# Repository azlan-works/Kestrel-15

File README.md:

# Kestrel-15: An Opensource FPGA SoM based on the Gowin GW5AT-15

1mm JLCPCB 6-layer 7628 stackup:

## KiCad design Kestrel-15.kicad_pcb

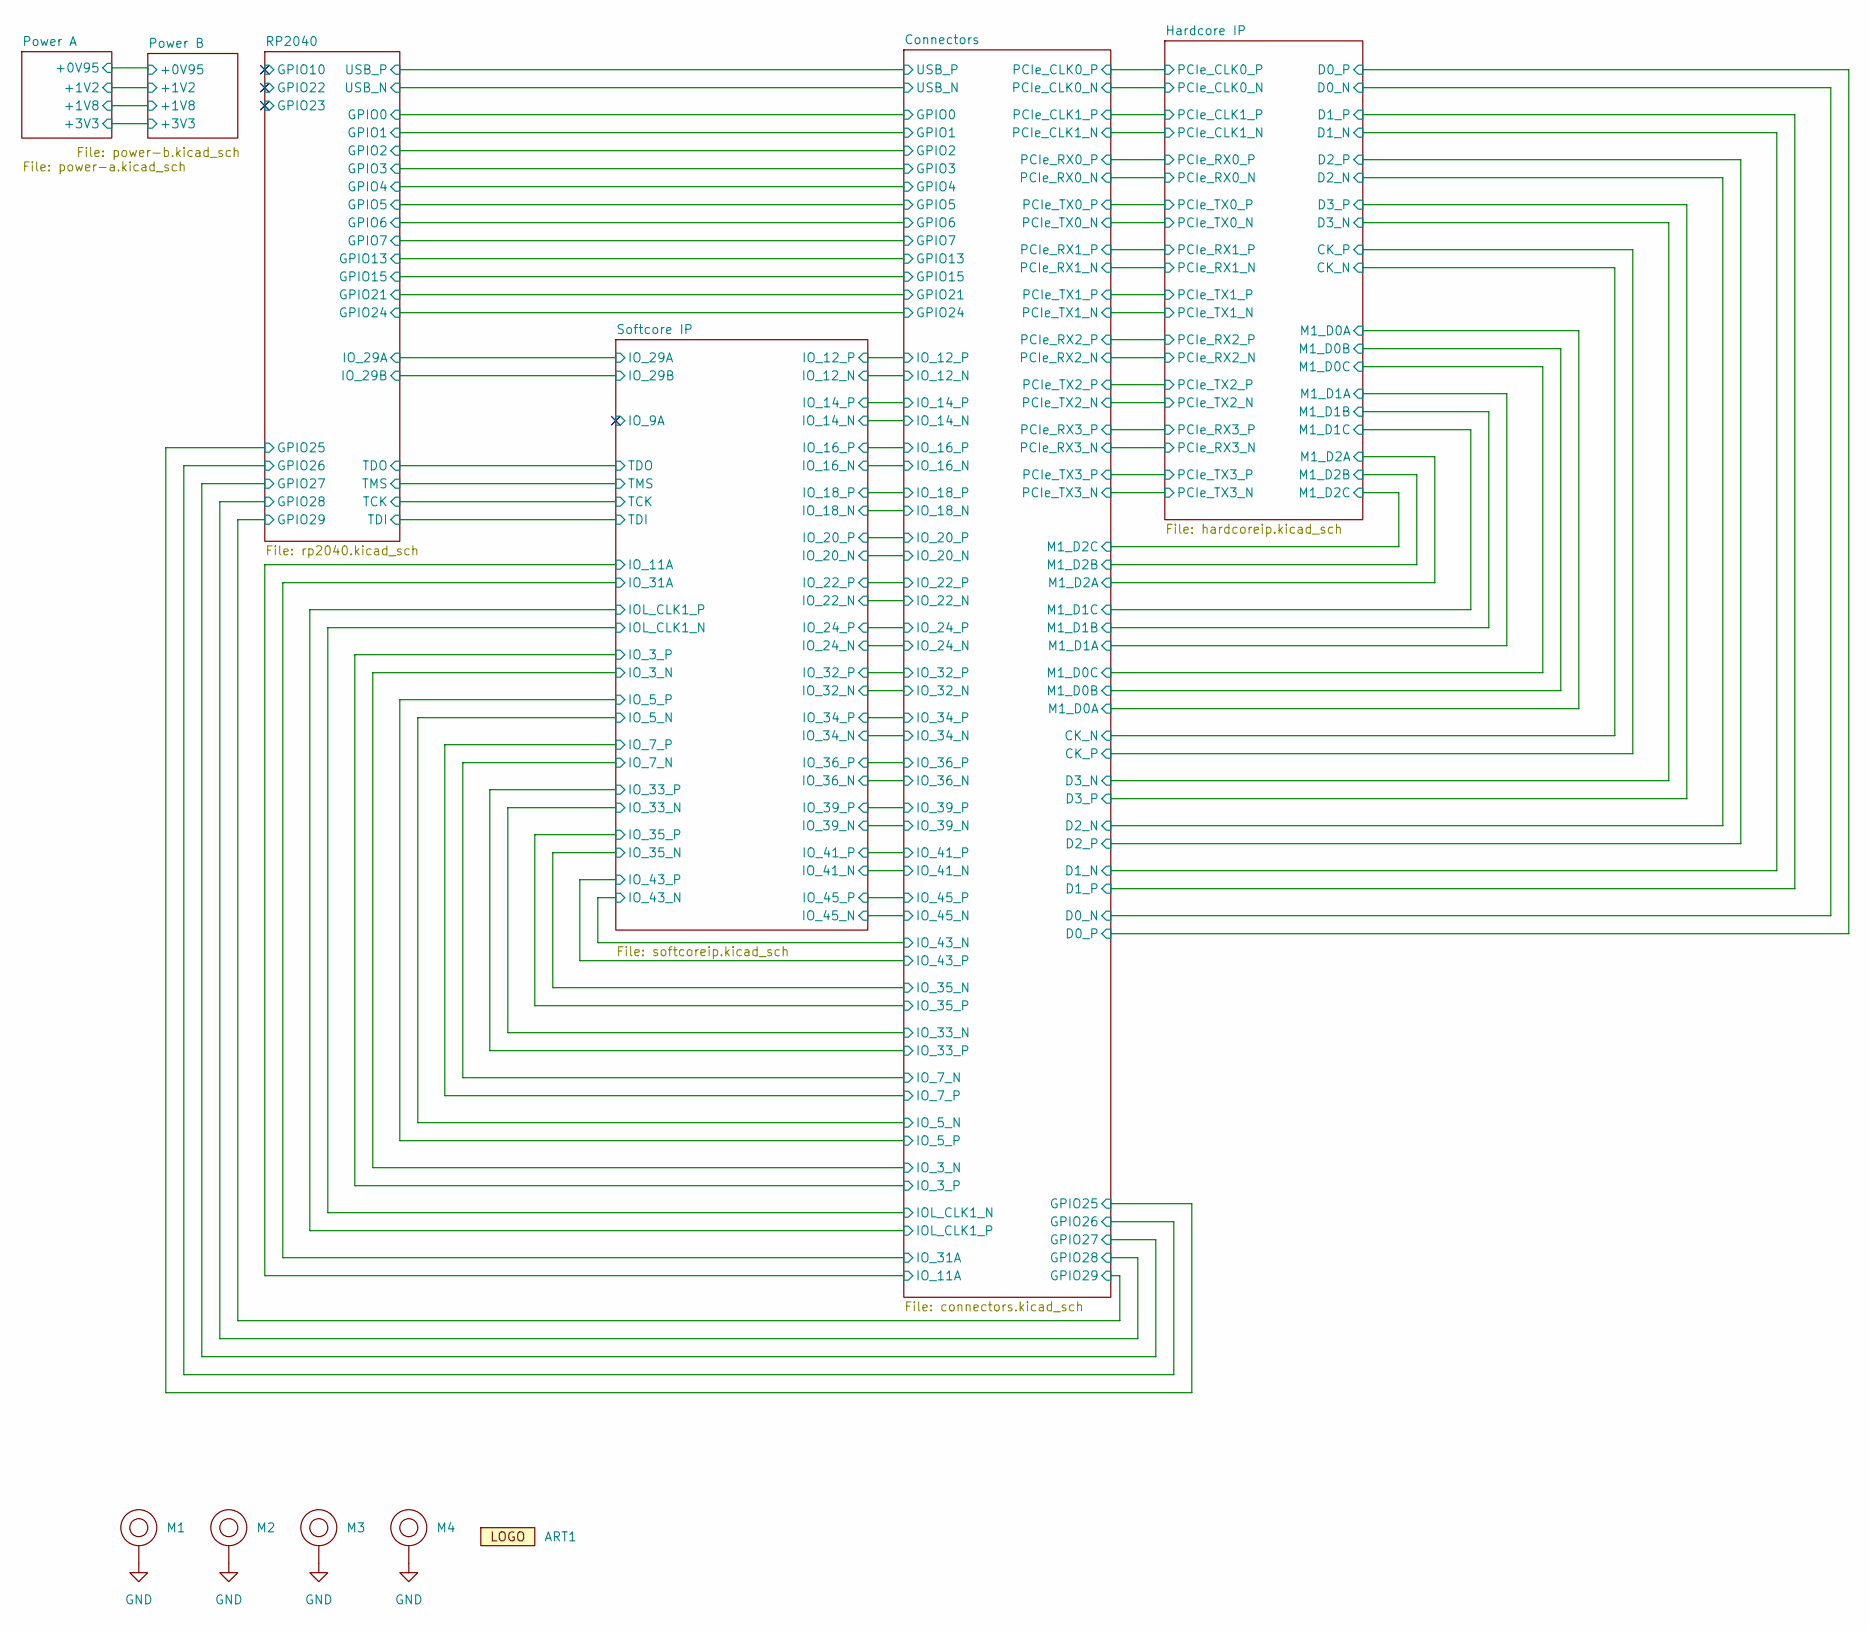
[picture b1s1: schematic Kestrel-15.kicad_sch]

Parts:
ART1: azlan.works_logo
M1, M2, M3, M4: M2_Hole

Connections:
GND: M1.1 (1_1), M2.1 (1_1), M3.1 (1_1), M4.1 (1_1); also elsewhere on the board

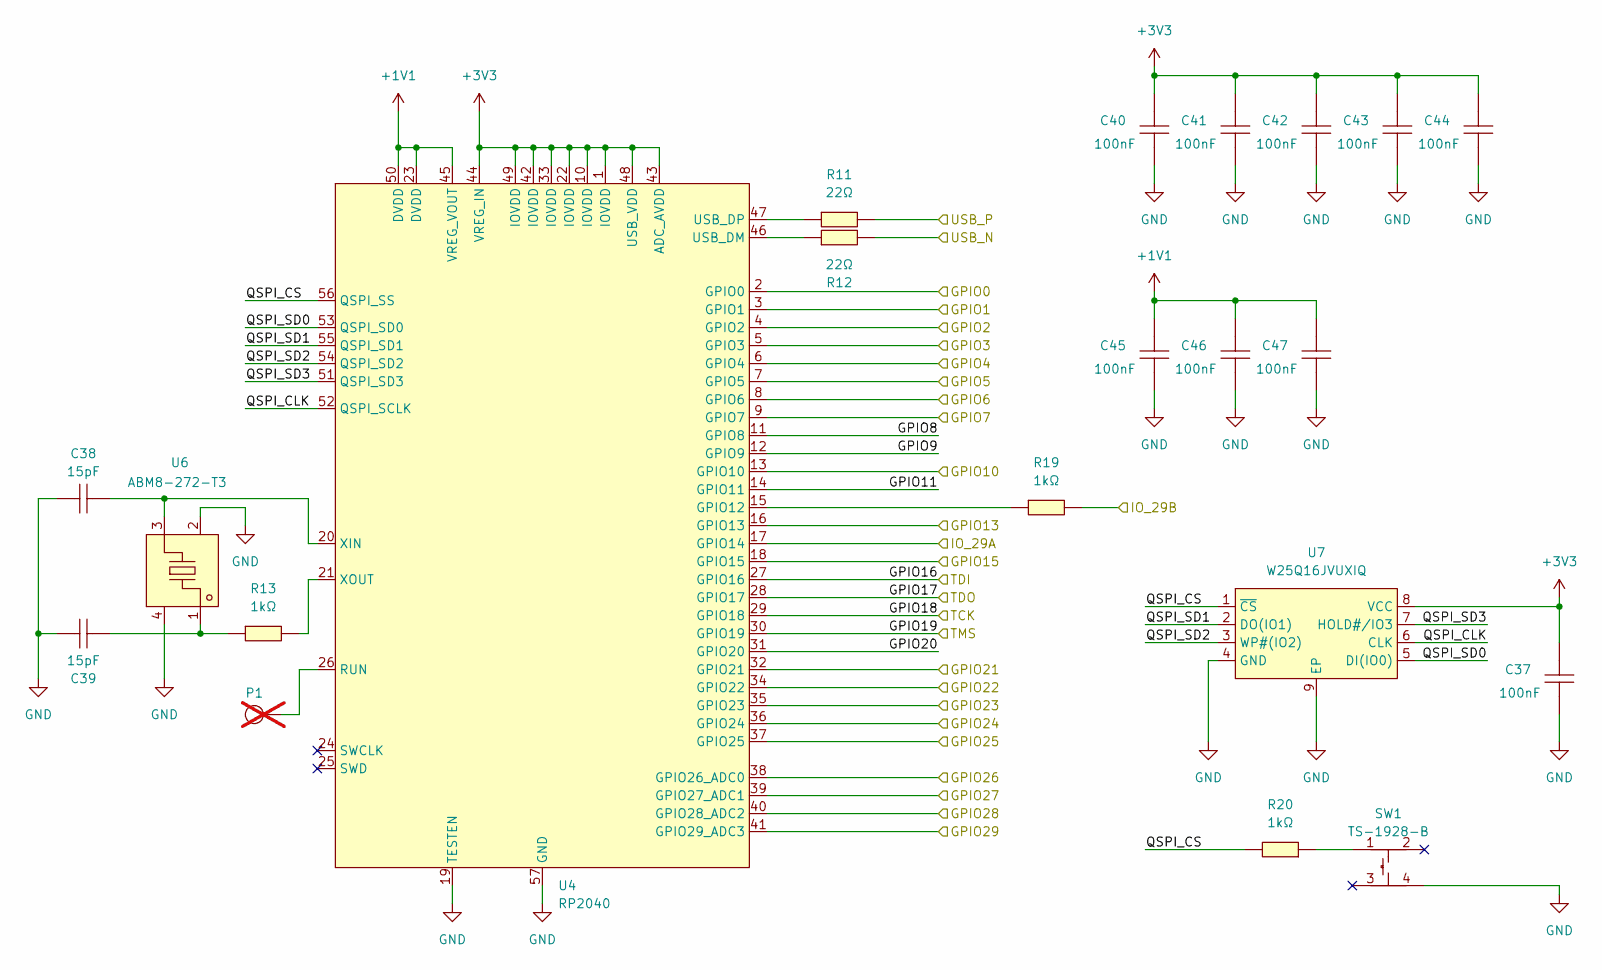
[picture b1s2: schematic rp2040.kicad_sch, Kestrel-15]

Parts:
C37, C40, C41, C42, C43, C44, C45, C46, C47: 100nF; C0201; MPN 0201X104M250NT; LCSC Part C52033358
C38, C39: 15pF; C0402; MPN 0402CG150J500NT; LCSC Part C1548
P1: Pogo Pin; TESTPOINT-SMD_BD2.0_C9900030651; MPN YTC1P-3010-01; LCSC Part C5221282; not fitted
R11, R12: 22Ω; R0402; MPN 0402WGF220JTCE; LCSC Part C25092
R13, R19, R20: 1kΩ; R0201; MPN 0201WMF1001TEE; LCSC Part C270365
SW1: TS-1928-B; KEY-SMD_4P-L2.8-W2.0-P1.20-LS3.0-TL; LCSC Part C1121891
U4: RP2040; LQFN-56_L7.0-W7.0-P0.4-EP; MPN RP2040; LCSC Part C2040
U6: ABM8-272-T3; CRYSTAL-SMD_4P-L3.2-W2.5-BL; MPN ABM8-272-T3; LCSC Part C20625731
U7: W25Q16JVUXIQ; USON-8_L3.0-W2.0-P0.50-BL-EP; MPN W25Q16JVUXIQ; LCSC Part C2843335

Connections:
+1V1: C45.2, C46.2, C47.2, U4.23 (DVDD), U4.45 (VREG_VOUT), U4.50 (DVDD)
+3V3: C37.2, C40.2, C41.2, C42.2, C43.2, C44.2, U4.1 (IOVDD), U4.10 (IOVDD), U4.22 (IOVDD), U4.33 (IOVDD), U4.42 (IOVDD), U4.43 (ADC_AVDD), U4.44 (VREG_IN), U4.48 (USB_VDD), U4.49 (IOVDD), U7.8 (VCC); also elsewhere on the board
/Connectors/GPIO0: U4.2 (GPIO0); also elsewhere on the board
/Connectors/GPIO1: U4.3 (GPIO1); also elsewhere on the board
/Connectors/GPIO2: U4.4 (GPIO2); also elsewhere on the board
/Connectors/GPIO3: U4.5 (GPIO3); also elsewhere on the board
/Connectors/GPIO4: U4.6 (GPIO4); also elsewhere on the board
/Connectors/GPIO5: U4.7 (GPIO5); also elsewhere on the board
/Connectors/GPIO6: U4.8 (GPIO6); also elsewhere on the board
/Connectors/GPIO7: U4.9 (GPIO7); also elsewhere on the board
/Connectors/GPIO13: U4.16 (GPIO13); also elsewhere on the board
/Connectors/GPIO15: U4.18 (GPIO15); also elsewhere on the board
/Connectors/GPIO21: U4.32 (GPIO21); also elsewhere on the board
/Connectors/GPIO24: U4.36 (GPIO24); also elsewhere on the board
/Connectors/GPIO25: U4.37 (GPIO25); also elsewhere on the board
/Connectors/GPIO26: U4.38 (GPIO26_ADC0); also elsewhere on the board
/Connectors/GPIO27: U4.39 (GPIO27_ADC1); also elsewhere on the board
/Connectors/GPIO28: U4.40 (GPIO28_ADC2); also elsewhere on the board
/Connectors/GPIO29: U4.41 (GPIO29_ADC3); also elsewhere on the board
/Connectors/USB_N: R12.2; also elsewhere on the board
/Connectors/USB_P: R11.2; also elsewhere on the board
/RP2040/GPIO8: U4.11 (GPIO8)
/RP2040/GPIO9: U4.12 (GPIO9)
/RP2040/GPIO10: U4.13 (GPIO10)
/RP2040/GPIO11: U4.14 (GPIO11)
/RP2040/GPIO16: U4.27 (GPIO16); also elsewhere on the board
/RP2040/GPIO17: U4.28 (GPIO17); also elsewhere on the board
/RP2040/GPIO18: U4.29 (GPIO18); also elsewhere on the board
/RP2040/GPIO19: U4.30 (GPIO19); also elsewhere on the board
/RP2040/GPIO20: U4.31 (GPIO20)
/RP2040/GPIO22: U4.34 (GPIO22)
/RP2040/GPIO23: U4.35 (GPIO23)
/RP2040/IO_29A: U4.17 (GPIO14); also elsewhere on the board
/RP2040/IO_29B: R19.2; also elsewhere on the board
/RP2040/QSPI_CLK: U4.52 (QSPI_SCLK), U7.6 (CLK)
/RP2040/QSPI_CS: R20.2, U4.56 (QSPI_SS), U7.1 (~CS)
/RP2040/QSPI_SD0: U4.53 (QSPI_SD0), U7.5 (DI(IO0))
/RP2040/QSPI_SD1: U4.55 (QSPI_SD1), U7.2 (DO(IO1))
/RP2040/QSPI_SD2: U4.54 (QSPI_SD2), U7.3 (WP#(IO2))
/RP2040/QSPI_SD3: U4.51 (QSPI_SD3), U7.7 (HOLD#/IO3)
GND: C37.1, C38.1, C39.1, C40.1, C41.1, C42.1, C43.1, C44.1, C45.1, C46.1, C47.1, SW1.4, U4.19 (TESTEN), U4.57 (GND), U6.2 (GND), U6.4 (GND), U7.4 (GND), U7.9 (EP); also elsewhere on the board
unnamed: C39.2, R13.1, U6.1
unnamed: R20.1, SW1.1
unnamed: R19.1, U4.15 (GPIO12)
unnamed: P1.1 (1_1), U4.26 (RUN)
unnamed: R12.1, U4.46 (USB_DM)
unnamed: R11.1, U4.47 (USB_DP)
unnamed: C38.2, U4.20 (XIN), U6.3
unnamed: R13.2, U4.21 (XOUT)

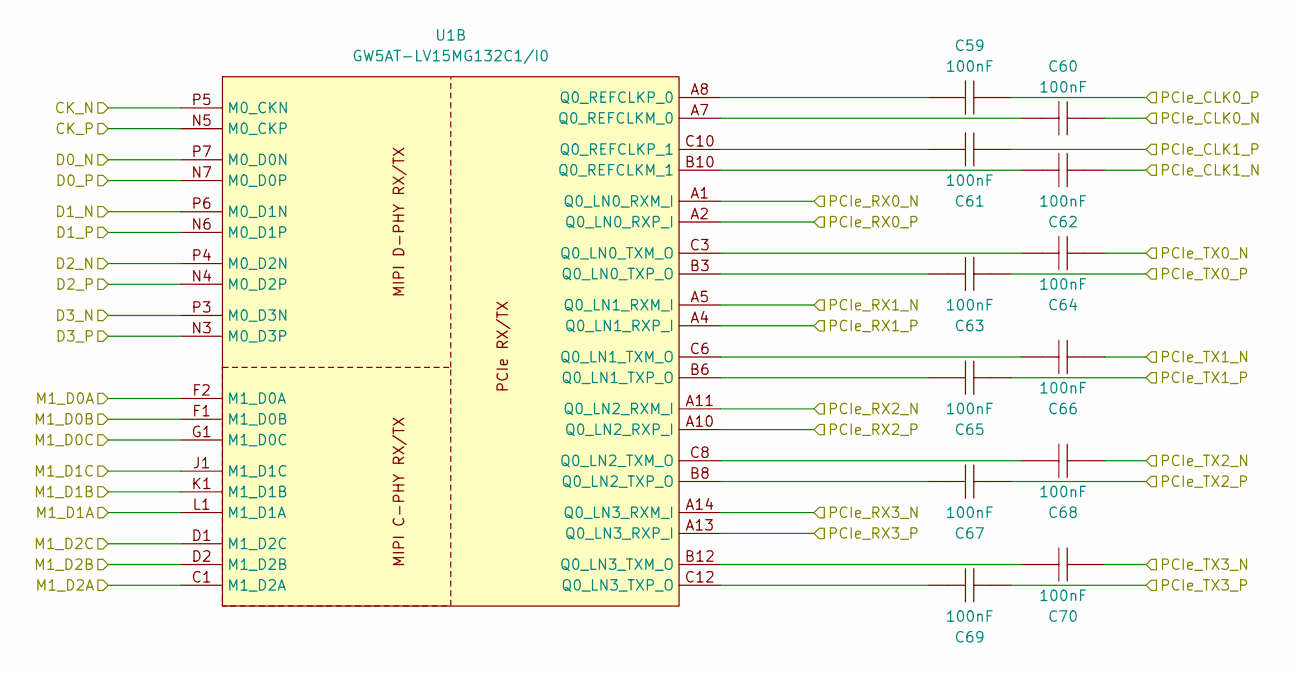
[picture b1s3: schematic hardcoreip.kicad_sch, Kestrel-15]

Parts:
C59, C60, C61, C62, C63, C64, C65, C66, C67, C68, C69, C70: 100nF; C0201; MPN 0201X104M250NT; LCSC Part C52033358
U1: GW5AT-LV15MG132C1/I0; CSBGA-132_L8.0-W8.0-P0.50-TL_GW1N-2K-MG132X1; MPN GW5AT-LV15MG132C1/I0; LCSC Part C54067362

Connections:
/Connectors/CK_N: U1.P5 (M0_CKN); also elsewhere on the board
/Connectors/CK_P: U1.N5 (M0_CKP); also elsewhere on the board
/Connectors/D0_N: U1.P7 (M0_D0N); also elsewhere on the board
/Connectors/D0_P: U1.N7 (M0_D0P); also elsewhere on the board
/Connectors/D1_N: U1.P6 (M0_D1N); also elsewhere on the board
/Connectors/D1_P: U1.N6 (M0_D1P); also elsewhere on the board
/Connectors/D2_N: U1.P4 (M0_D2N); also elsewhere on the board
/Connectors/D2_P: U1.N4 (M0_D2P); also elsewhere on the board
/Connectors/D3_N: U1.P3 (M0_D3N); also elsewhere on the board
/Connectors/D3_P: U1.N3 (M0_D3P); also elsewhere on the board
/Connectors/M1_D0A: U1.F2 (M1_D0A); also elsewhere on the board
/Connectors/M1_D0B: U1.F1 (M1_D0B); also elsewhere on the board
/Connectors/M1_D0C: U1.G1 (M1_D0C); also elsewhere on the board
/Connectors/M1_D1A: U1.L1 (M1_D1A); also elsewhere on the board
/Connectors/M1_D1B: U1.K1 (M1_D1B); also elsewhere on the board
/Connectors/M1_D1C: U1.J1 (M1_D1C); also elsewhere on the board
/Connectors/M1_D2A: U1.C1 (M1_D2A); also elsewhere on the board
/Connectors/M1_D2B: U1.D2 (M1_D2B); also elsewhere on the board
/Connectors/M1_D2C: U1.D1 (M1_D2C); also elsewhere on the board
/Connectors/PCIe_CLK0_N: C60.2; also elsewhere on the board
/Connectors/PCIe_CLK0_P: C59.2; also elsewhere on the board
/Connectors/PCIe_CLK1_N: C62.2; also elsewhere on the board
/Connectors/PCIe_CLK1_P: C61.2; also elsewhere on the board
/Connectors/PCIe_RX0_N: U1.A1 (Q0_LN0_RXM_I); also elsewhere on the board
/Connectors/PCIe_RX0_P: U1.A2 (Q0_LN0_RXP_I); also elsewhere on the board
/Connectors/PCIe_RX1_N: U1.A5 (Q0_LN1_RXM_I); also elsewhere on the board
/Connectors/PCIe_RX1_P: U1.A4 (Q0_LN1_RXP_I); also elsewhere on the board
/Connectors/PCIe_RX2_N: U1.A11 (Q0_LN2_RXM_I); also elsewhere on the board
/Connectors/PCIe_RX2_P: U1.A10 (Q0_LN2_RXP_I); also elsewhere on the board
/Connectors/PCIe_RX3_N: U1.A14 (Q0_LN3_RXM_I); also elsewhere on the board
/Connectors/PCIe_RX3_P: U1.A13 (Q0_LN3_RXP_I); also elsewhere on the board
/Connectors/PCIe_TX0_N: C64.2; also elsewhere on the board
/Connectors/PCIe_TX0_P: C63.2; also elsewhere on the board
/Connectors/PCIe_TX1_N: C66.2; also elsewhere on the board
/Connectors/PCIe_TX1_P: C65.2; also elsewhere on the board
/Connectors/PCIe_TX2_N: C68.2; also elsewhere on the board
/Connectors/PCIe_TX2_P: C67.2; also elsewhere on the board
/Connectors/PCIe_TX3_N: C70.2; also elsewhere on the board
/Connectors/PCIe_TX3_P: C69.2; also elsewhere on the board
unnamed: C64.1, U1.C3 (Q0_LN0_TXM_O)
unnamed: C63.1, U1.B3 (Q0_LN0_TXP_O)
unnamed: C66.1, U1.C6 (Q0_LN1_TXM_O)
unnamed: C65.1, U1.B6 (Q0_LN1_TXP_O)
unnamed: C68.1, U1.C8 (Q0_LN2_TXM_O)
unnamed: C67.1, U1.B8 (Q0_LN2_TXP_O)
unnamed: C70.1, U1.B12 (Q0_LN3_TXM_O)
unnamed: C69.1, U1.C12 (Q0_LN3_TXP_O)
unnamed: C60.1, U1.A7 (Q0_REFCLKM_0)
unnamed: C62.1, U1.B10 (Q0_REFCLKM_1)
unnamed: C59.1, U1.A8 (Q0_REFCLKP_0)
unnamed: C61.1, U1.C10 (Q0_REFCLKP_1)

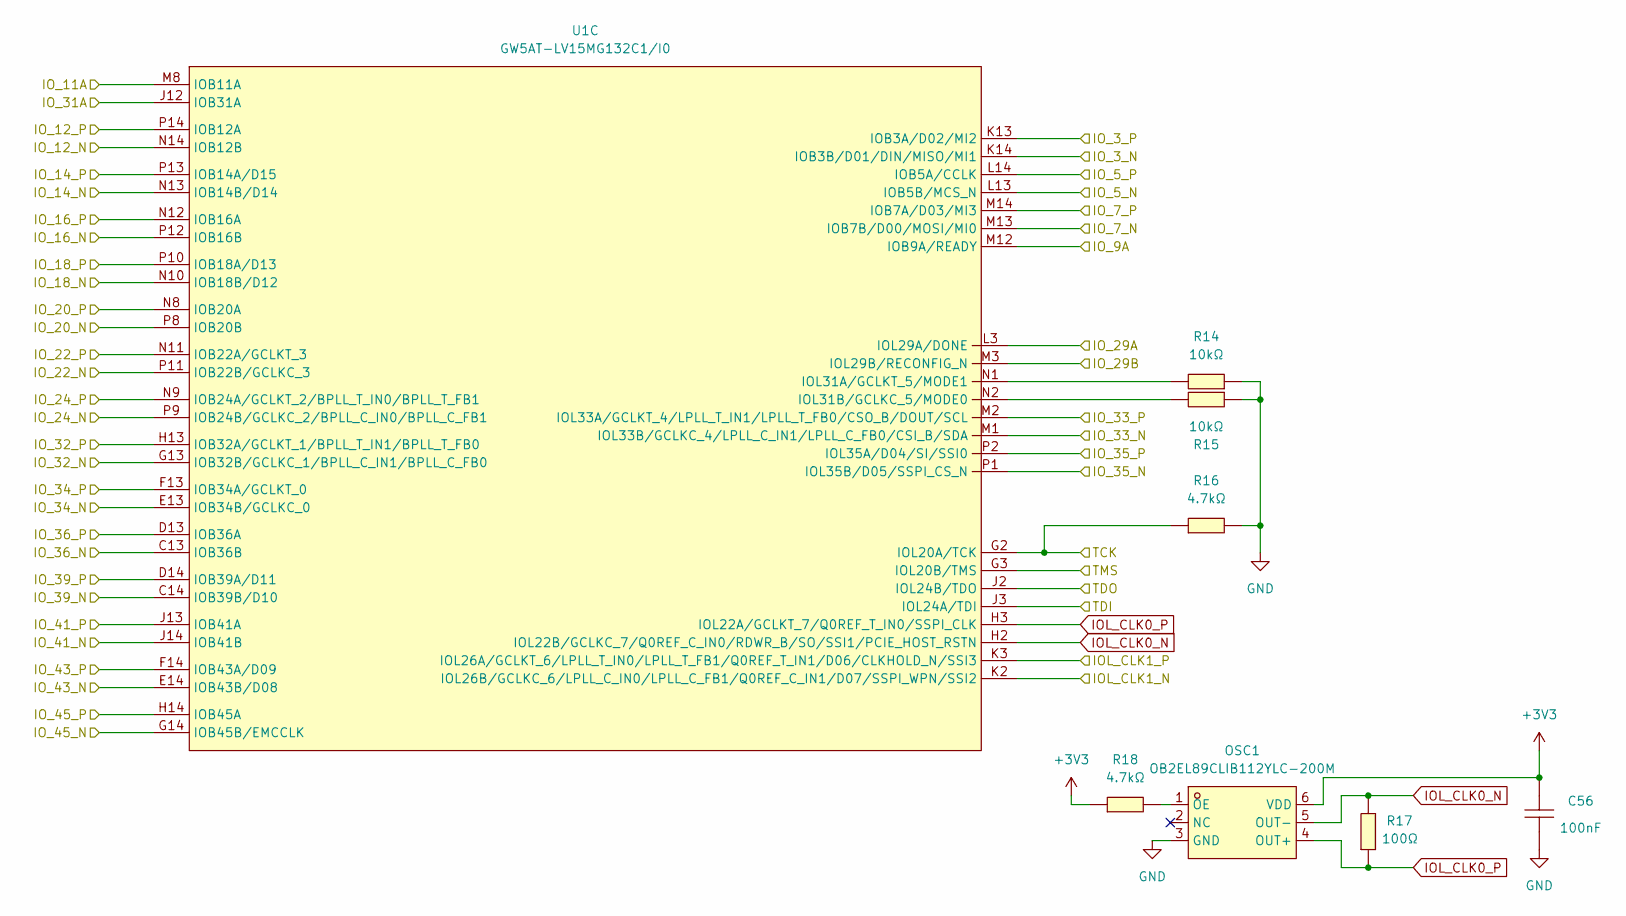
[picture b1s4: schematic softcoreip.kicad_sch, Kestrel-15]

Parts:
C56: 100nF; C0201; MPN 0201X104M250NT; LCSC Part C52033358
OSC1: OB2EL89CLIB112YLC-200M; OSC-SMD_6P-L3.2-W2.5-BL-1; MPN OB2EL89CLIB112YLC-200M; LCSC Part C41371042
R14, R15: 10kΩ; R0402; MPN 0402WGF1002TCE; LCSC Part C25744
R16, R18: 4.7kΩ; R0402; MPN 0402WGF4701TCE; LCSC Part C25900
R17: 100Ω; R0402; MPN 0402WGF1000TCE; LCSC Part C25076
U1: GW5AT-LV15MG132C1/I0; CSBGA-132_L8.0-W8.0-P0.50-TL_GW1N-2K-MG132X1; MPN GW5AT-LV15MG132C1/I0; LCSC Part C54067362

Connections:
+3V3: C56.2, OSC1.6 (VDD), R18.1; also elsewhere on the board
/Connectors/IOL_CLK1_N: U1.K2 (IOL26B/GCLKC_6/LPLL_C_IN0/LPLL_C_FB1/Q0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); also elsewhere on the board
/Connectors/IOL_CLK1_P: U1.K3 (IOL26A/GCLKT_6/LPLL_T_IN0/LPLL_T_FB1/Q0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); also elsewhere on the board
/Connectors/IO_3_N: U1.K14 (IOB3B/D01/DIN/MISO/MI1); also elsewhere on the board
/Connectors/IO_3_P: U1.K13 (IOB3A/D02/MI2); also elsewhere on the board
/Connectors/IO_5_N: U1.L13 (IOB5B/MCS_N); also elsewhere on the board
/Connectors/IO_5_P: U1.L14 (IOB5A/CCLK); also elsewhere on the board
/Connectors/IO_7_N: U1.M13 (IOB7B/D00/MOSI/MI0); also elsewhere on the board
/Connectors/IO_7_P: U1.M14 (IOB7A/D03/MI3); also elsewhere on the board
/Connectors/IO_11A: U1.M8 (IOB11A); also elsewhere on the board
/Connectors/IO_12_N: U1.N14 (IOB12B); also elsewhere on the board
/Connectors/IO_12_P: U1.P14 (IOB12A); also elsewhere on the board
/Connectors/IO_14_N: U1.N13 (IOB14B/D14); also elsewhere on the board
/Connectors/IO_14_P: U1.P13 (IOB14A/D15); also elsewhere on the board
/Connectors/IO_16_N: U1.P12 (IOB16B); also elsewhere on the board
/Connectors/IO_16_P: U1.N12 (IOB16A); also elsewhere on the board
/Connectors/IO_18_N: U1.N10 (IOB18B/D12); also elsewhere on the board
/Connectors/IO_18_P: U1.P10 (IOB18A/D13); also elsewhere on the board
/Connectors/IO_20_N: U1.P8 (IOB20B); also elsewhere on the board
/Connectors/IO_20_P: U1.N8 (IOB20A); also elsewhere on the board
/Connectors/IO_22_N: U1.P11 (IOB22B/GCLKC_3); also elsewhere on the board
/Connectors/IO_22_P: U1.N11 (IOB22A/GCLKT_3); also elsewhere on the board
/Connectors/IO_24_N: U1.P9 (IOB24B/GCLKC_2/BPLL_C_IN0/BPLL_C_FB1); also elsewhere on the board
/Connectors/IO_24_P: U1.N9 (IOB24A/GCLKT_2/BPLL_T_IN0/BPLL_T_FB1); also elsewhere on the board
/Connectors/IO_31A: U1.J12 (IOB31A); also elsewhere on the board
/Connectors/IO_32_N: U1.G13 (IOB32B/GCLKC_1/BPLL_C_IN1/BPLL_C_FB0); also elsewhere on the board
/Connectors/IO_32_P: U1.H13 (IOB32A/GCLKT_1/BPLL_T_IN1/BPLL_T_FB0); also elsewhere on the board
/Connectors/IO_33_N: U1.M1 (IOL33B/GCLKC_4/LPLL_C_IN1/LPLL_C_FB0/CS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); also elsewhere on the board
/Connectors/IO_33_P: U1.M2 (IOL33A/GCLKT_4/LPLL_T_IN1/LPLL_T_FB0/CS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); also elsewhere on the board
/Connectors/IO_34_N: U1.E13 (IOB34B/GCLKC_0); also elsewhere on the board
/Connectors/IO_34_P: U1.F13 (IOB34A/GCLKT_0); also elsewhere on the board
/Connectors/IO_35_N: U1.P1 (IOL35B/D05/SSPI_CS_N); also elsewhere on the board
/Connectors/IO_35_P: U1.P2 (IOL35A/D04/SI/SSI0); also elsewhere on the board
/Connectors/IO_36_N: U1.C13 (IOB36B); also elsewhere on the board
/Connectors/IO_36_P: U1.D13 (IOB36A); also elsewhere on the board
/Connectors/IO_39_N: U1.C14 (IOB39B/D10); also elsewhere on the board
/Connectors/IO_39_P: U1.D14 (IOB39A/D11); also elsewhere on the board
/Connectors/IO_41_N: U1.J14 (IOB41B); also elsewhere on the board
/Connectors/IO_41_P: U1.J13 (IOB41A); also elsewhere on the board
/Connectors/IO_43_N: U1.E14 (IOB43B/D08); also elsewhere on the board
/Connectors/IO_43_P: U1.F14 (IOB43A/D09); also elsewhere on the board
/Connectors/IO_45_N: U1.G14 (IOB45B/EMCCLK); also elsewhere on the board
/Connectors/IO_45_P: U1.H14 (IOB45A); also elsewhere on the board
/RP2040/GPIO16: U1.J3 (IOL24A/TDI); also elsewhere on the board
/RP2040/GPIO17: U1.J2 (IOL24B/TDO); also elsewhere on the board
/RP2040/GPIO18: R16.1, U1.G2 (IOL20A/TCK); also elsewhere on the board
/RP2040/GPIO19: U1.G3 (IOL20B/TMS); also elsewhere on the board
/RP2040/IO_29A: U1.L3 (IOL29A/DONE); also elsewhere on the board
/RP2040/IO_29B: U1.M3 (IOL29B/RECONFIG_N); also elsewhere on the board
/Softcore IP/IO_9A: U1.M12 (IOB9A/READY)
GND: C56.1, OSC1.3 (GND), R14.1, R15.1, R16.2; also elsewhere on the board
IOL_CLK0_N: OSC1.5 (OUT-), R17.2, U1.H2 (IOL22B/GCLKC_7/Q0REF_C_IN0/RDWR_B/SO/SS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)
IOL_CLK0_P: OSC1.4 (OUT+), R17.1, U1.H3 (IOL22A/GCLKT_7/Q0REF_T_IN0/SSPI_CLK)
unnamed: OSC1.1 (OE), R18.2
unnamed: R14.2, U1.N1 (IOL31A/GCLKT_5/MODE1)
unnamed: R15.2, U1.N2 (IOL31B/GCLKC_5/MODE0)

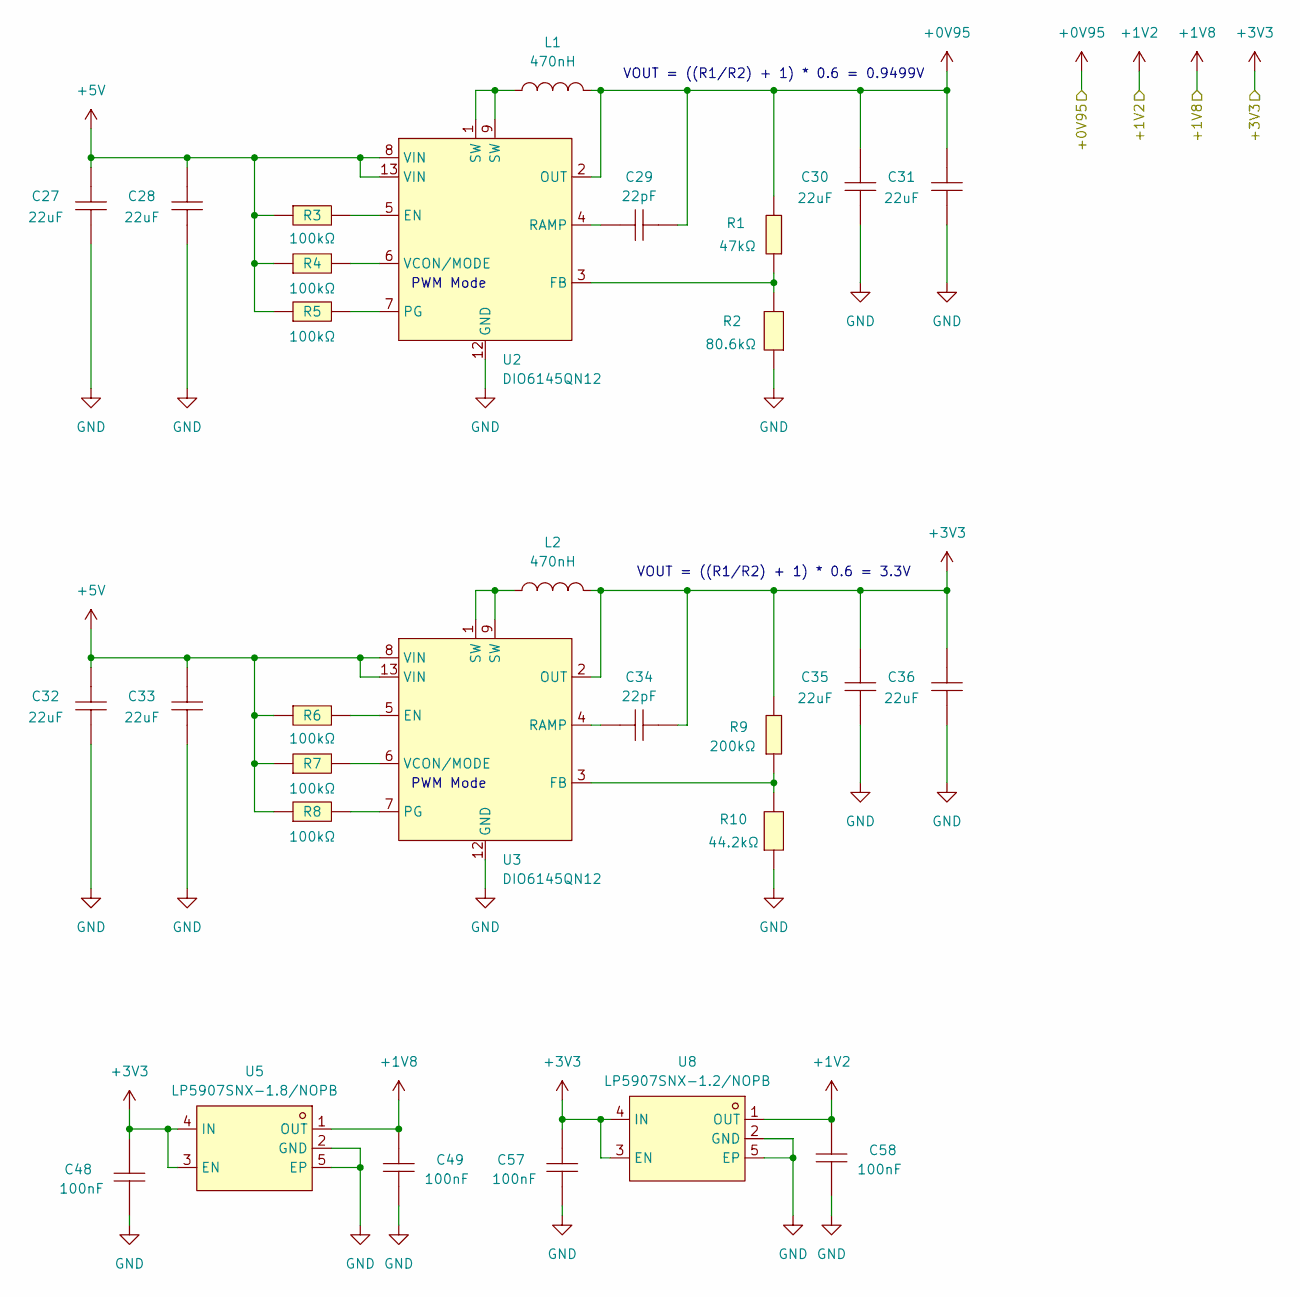
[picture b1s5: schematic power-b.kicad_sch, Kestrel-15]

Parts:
C27, C28, C30, C31, C32, C33, C35, C36: 22uF; C0603; MPN CL10A226MQ8NRNC; LCSC Part C59461
C29, C34: 22pF; C0201; MPN C0603C0G1H220JT00NN; LCSC Part C49296932
C48, C49, C57, C58: 100nF; C0201; MPN 0201X104M250NT; LCSC Part C52033358
L1, L2: 470nH; IND-SMD_L2.5-W2.0_FTC252010S; MPN FTC252010SR47MBCA; LCSC Part C5832354
R1: 47kΩ; R0201; MPN PF01WMF4702TEE; LCSC Part C50670294
R2: 80.6kΩ; R0201; MPN NQ01WMF8062TEE; LCSC Part C50670129
R3, R4, R5, R6, R7, R8: 100kΩ; R0201; MPN PF01WMF1003TEE; LCSC Part C50670353
R9: 200kΩ; R0201; MPN 0201WMF2003TEE; LCSC Part C270357
R10: 44.2kΩ; R0201; MPN GR0201F44K2TAG00; LCSC Part C49655072
U2, U3: DIO6145QN12; QFN-12_L3.0-W2.0-P0.50_DIO6145QN12; MPN DIO6145QN12; LCSC Part C2980987
U5: LP5907SNX-1.8/NOPB; ZQFN-4L_L1.0-W1.0-P0.63-BL-EP; MPN LP5907SNX-1.8/NOPB; LCSC Part C139378
U8: LP5907SNX-1.2/NOPB; ZQFN-4L_L1.0-W1.0-P0.63-BL-EP; MPN LP5907SNX-1.2/NOPB; LCSC Part C165128

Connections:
+0V95: C29.2, C30.2, C31.2, L1.2, R1.2, U2.2 (OUT); also elsewhere on the board
+1V2: C58.2, U8.1 (OUT); also elsewhere on the board
+1V8: C49.2, U5.1 (OUT); also elsewhere on the board
+3V3: C34.2, C35.2, C36.2, C48.2, C57.2, L2.2, R9.2, U3.2 (OUT), U5.3 (EN), U5.4 (IN), U8.3 (EN), U8.4 (IN); also elsewhere on the board
+5V: C27.2, C28.2, C32.2, C33.2, R3.1, R4.1, R5.1, R6.1, R7.1, R8.1, U2.8 (VIN), U2.13 (VIN), U3.8 (VIN), U3.13 (VIN); also elsewhere on the board
GND: C27.1, C28.1, C30.1, C31.1, C32.1, C33.1, C35.1, C36.1, C48.1, C49.1, C57.1, C58.1, R2.1, R10.1, U2.12 (GND), U3.12 (GND), U5.2 (GND), U5.5 (EP), U8.2 (GND), U8.5 (EP); also elsewhere on the board
unnamed: L1.1, U2.1 (SW), U2.9 (SW)
unnamed: L2.1, U3.1 (SW), U3.9 (SW)
unnamed: R3.2, U2.5 (EN)
unnamed: R1.1, R2.2, U2.3 (FB)
unnamed: R5.2, U2.7 (PG)
unnamed: C29.1, U2.4 (RAMP)
unnamed: R4.2, U2.6 (VCON/MODE)
unnamed: R6.2, U3.5 (EN)
unnamed: R9.1, R10.2, U3.3 (FB)
unnamed: R8.2, U3.7 (PG)
unnamed: C34.1, U3.4 (RAMP)
unnamed: R7.2, U3.6 (VCON/MODE)

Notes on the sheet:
VOUT = ((R1/R2) + 1) * 0.6 = 3.3V
PWM Mode
VOUT = ((R1/R2) + 1) * 0.6 = 0.9499V

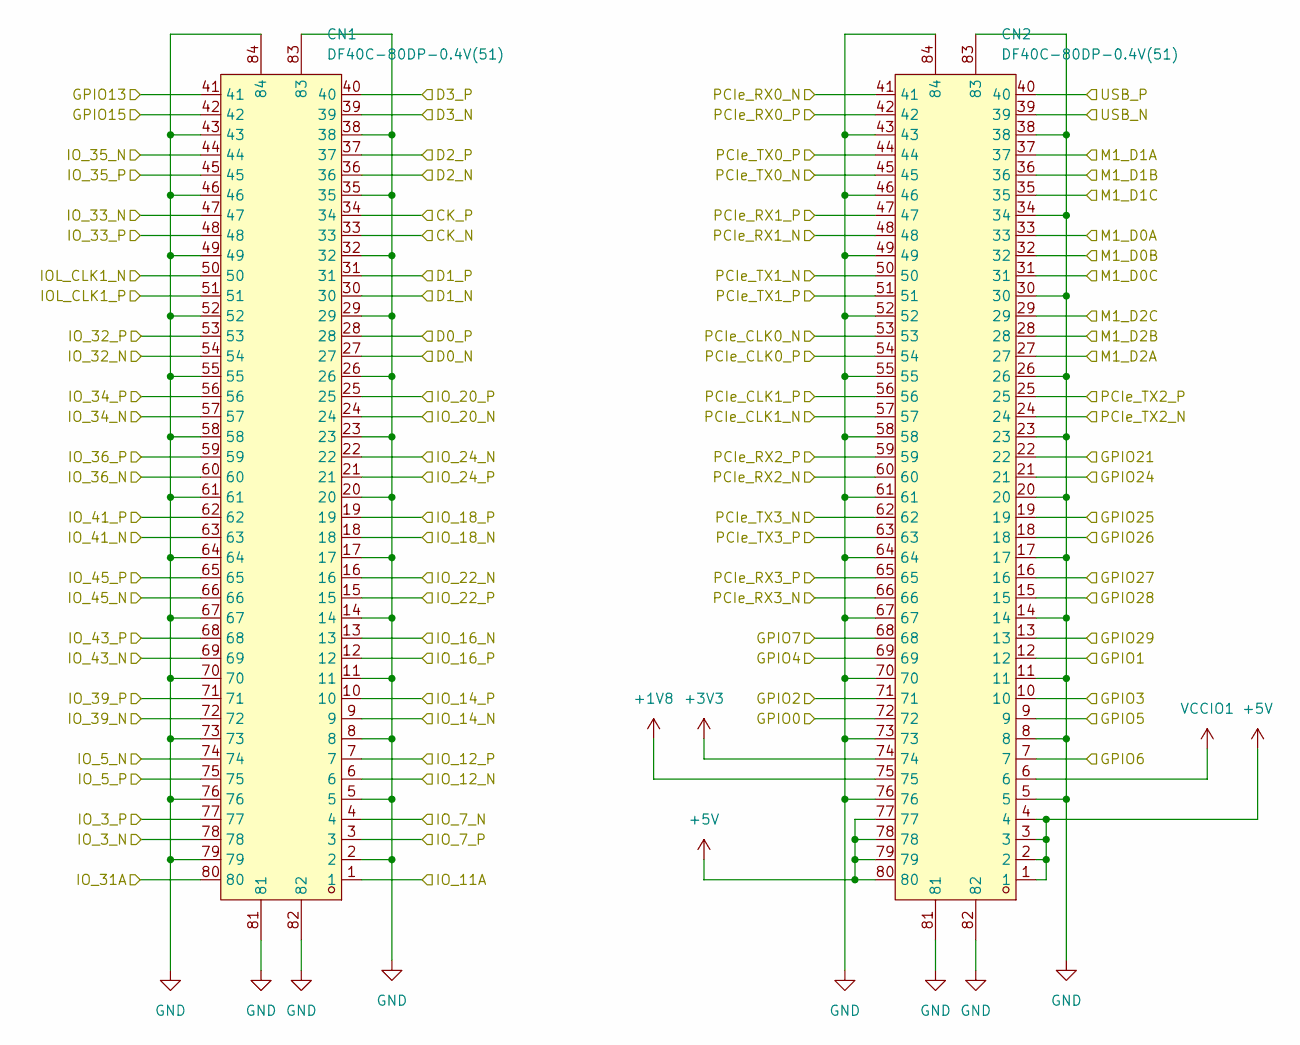
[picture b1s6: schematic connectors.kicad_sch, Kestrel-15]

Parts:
CN1, CN2: DF40C-80DP-0.4V(51); CONN-SMD_DF40C-80DP-0.4V-51; MPN DF40C-80DP-0.4V(51); LCSC Part C294544

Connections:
+1V8: CN2.75; also elsewhere on the board
+3V3: CN2.74; also elsewhere on the board
+5V: CN2.1, CN2.2, CN2.3, CN2.4, CN2.77, CN2.78, CN2.79, CN2.80; also elsewhere on the board
/Connectors/CK_N: CN1.33; also elsewhere on the board
/Connectors/CK_P: CN1.34; also elsewhere on the board
/Connectors/D0_N: CN1.27; also elsewhere on the board
/Connectors/D0_P: CN1.28; also elsewhere on the board
/Connectors/D1_N: CN1.30; also elsewhere on the board
/Connectors/D1_P: CN1.31; also elsewhere on the board
/Connectors/D2_N: CN1.36; also elsewhere on the board
/Connectors/D2_P: CN1.37; also elsewhere on the board
/Connectors/D3_N: CN1.39; also elsewhere on the board
/Connectors/D3_P: CN1.40; also elsewhere on the board
/Connectors/GPIO0: CN2.72; also elsewhere on the board
/Connectors/GPIO1: CN2.12; also elsewhere on the board
/Connectors/GPIO2: CN2.71; also elsewhere on the board
/Connectors/GPIO3: CN2.10; also elsewhere on the board
/Connectors/GPIO4: CN2.69; also elsewhere on the board
/Connectors/GPIO5: CN2.9; also elsewhere on the board
/Connectors/GPIO6: CN2.7; also elsewhere on the board
/Connectors/GPIO7: CN2.68; also elsewhere on the board
/Connectors/GPIO13: CN1.41; also elsewhere on the board
/Connectors/GPIO15: CN1.42; also elsewhere on the board
/Connectors/GPIO21: CN2.22; also elsewhere on the board
/Connectors/GPIO24: CN2.21; also elsewhere on the board
/Connectors/GPIO25: CN2.19; also elsewhere on the board
/Connectors/GPIO26: CN2.18; also elsewhere on the board
/Connectors/GPIO27: CN2.16; also elsewhere on the board
/Connectors/GPIO28: CN2.15; also elsewhere on the board
/Connectors/GPIO29: CN2.13; also elsewhere on the board
/Connectors/IOL_CLK1_N: CN1.50; also elsewhere on the board
/Connectors/IOL_CLK1_P: CN1.51; also elsewhere on the board
/Connectors/IO_3_N: CN1.78; also elsewhere on the board
/Connectors/IO_3_P: CN1.77; also elsewhere on the board
/Connectors/IO_5_N: CN1.74; also elsewhere on the board
/Connectors/IO_5_P: CN1.75; also elsewhere on the board
/Connectors/IO_7_N: CN1.4; also elsewhere on the board
/Connectors/IO_7_P: CN1.3; also elsewhere on the board
/Connectors/IO_11A: CN1.1; also elsewhere on the board
/Connectors/IO_12_N: CN1.6; also elsewhere on the board
/Connectors/IO_12_P: CN1.7; also elsewhere on the board
/Connectors/IO_14_N: CN1.9; also elsewhere on the board
/Connectors/IO_14_P: CN1.10; also elsewhere on the board
/Connectors/IO_16_N: CN1.13; also elsewhere on the board
/Connectors/IO_16_P: CN1.12; also elsewhere on the board
/Connectors/IO_18_N: CN1.18; also elsewhere on the board
/Connectors/IO_18_P: CN1.19; also elsewhere on the board
/Connectors/IO_20_N: CN1.24; also elsewhere on the board
/Connectors/IO_20_P: CN1.25; also elsewhere on the board
/Connectors/IO_22_N: CN1.16; also elsewhere on the board
/Connectors/IO_22_P: CN1.15; also elsewhere on the board
/Connectors/IO_24_N: CN1.22; also elsewhere on the board
/Connectors/IO_24_P: CN1.21; also elsewhere on the board
/Connectors/IO_31A: CN1.80; also elsewhere on the board
/Connectors/IO_32_N: CN1.54; also elsewhere on the board
/Connectors/IO_32_P: CN1.53; also elsewhere on the board
/Connectors/IO_33_N: CN1.47; also elsewhere on the board
/Connectors/IO_33_P: CN1.48; also elsewhere on the board
/Connectors/IO_34_N: CN1.57; also elsewhere on the board
/Connectors/IO_34_P: CN1.56; also elsewhere on the board
/Connectors/IO_35_N: CN1.44; also elsewhere on the board
/Connectors/IO_35_P: CN1.45; also elsewhere on the board
/Connectors/IO_36_N: CN1.60; also elsewhere on the board
/Connectors/IO_36_P: CN1.59; also elsewhere on the board
/Connectors/IO_39_N: CN1.72; also elsewhere on the board
/Connectors/IO_39_P: CN1.71; also elsewhere on the board
/Connectors/IO_41_N: CN1.63; also elsewhere on the board
/Connectors/IO_41_P: CN1.62; also elsewhere on the board
/Connectors/IO_43_N: CN1.69; also elsewhere on the board
/Connectors/IO_43_P: CN1.68; also elsewhere on the board
/Connectors/IO_45_N: CN1.66; also elsewhere on the board
/Connectors/IO_45_P: CN1.65; also elsewhere on the board
/Connectors/M1_D0A: CN2.33; also elsewhere on the board
/Connectors/M1_D0B: CN2.32; also elsewhere on the board
/Connectors/M1_D0C: CN2.31; also elsewhere on the board
/Connectors/M1_D1A: CN2.37; also elsewhere on the board
/Connectors/M1_D1B: CN2.36; also elsewhere on the board
/Connectors/M1_D1C: CN2.35; also elsewhere on the board
/Connectors/M1_D2A: CN2.27; also elsewhere on the board
/Connectors/M1_D2B: CN2.28; also elsewhere on the board
/Connectors/M1_D2C: CN2.29; also elsewhere on the board
/Connectors/PCIe_CLK0_N: CN2.53; also elsewhere on the board
/Connectors/PCIe_CLK0_P: CN2.54; also elsewhere on the board
/Connectors/PCIe_CLK1_N: CN2.57; also elsewhere on the board
/Connectors/PCIe_CLK1_P: CN2.56; also elsewhere on the board
/Connectors/PCIe_RX0_N: CN2.41; also elsewhere on the board
/Connectors/PCIe_RX0_P: CN2.42; also elsewhere on the board
/Connectors/PCIe_RX1_N: CN2.48; also elsewhere on the board
/Connectors/PCIe_RX1_P: CN2.47; also elsewhere on the board
/Connectors/PCIe_RX2_N: CN2.60; also elsewhere on the board
/Connectors/PCIe_RX2_P: CN2.59; also elsewhere on the board
/Connectors/PCIe_RX3_N: CN2.66; also elsewhere on the board
/Connectors/PCIe_RX3_P: CN2.65; also elsewhere on the board
/Connectors/PCIe_TX0_N: CN2.45; also elsewhere on the board
/Connectors/PCIe_TX0_P: CN2.44; also elsewhere on the board
/Connectors/PCIe_TX1_N: CN2.50; also elsewhere on the board
/Connectors/PCIe_TX1_P: CN2.51; also elsewhere on the board
/Connectors/PCIe_TX2_N: CN2.24; also elsewhere on the board
/Connectors/PCIe_TX2_P: CN2.25; also elsewhere on the board
/Connectors/PCIe_TX3_N: CN2.62; also elsewhere on the board
/Connectors/PCIe_TX3_P: CN2.63; also elsewhere on the board
/Connectors/USB_N: CN2.39; also elsewhere on the board
/Connectors/USB_P: CN2.40; also elsewhere on the board
GND: CN1.2, CN1.5, CN1.8, CN1.11, CN1.14, CN1.17, CN1.20, CN1.23, CN1.26, CN1.29, CN1.32, CN1.35, CN1.38, CN1.43, CN1.46, CN1.49, CN1.52, CN1.55, CN1.58, CN1.61, CN1.64, CN1.67, CN1.70, CN1.73, CN1.76, CN1.79, CN1.81, CN1.82, CN1.83, CN1.84, CN2.5, CN2.8, CN2.11, CN2.14, CN2.17, CN2.20, CN2.23, CN2.26, CN2.30, CN2.34, CN2.38, CN2.43, CN2.46, CN2.49, CN2.52, CN2.55, CN2.58, CN2.61, CN2.64, CN2.67, CN2.70, CN2.73, CN2.76, CN2.81, CN2.82, CN2.83, CN2.84; also elsewhere on the board
VCCIO1: CN2.6; also elsewhere on the board
